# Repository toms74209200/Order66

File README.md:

<h1 style="text-align: center; margin-top: 0; margin-bottom: 7rem; border-bottom: none;">Order66 - 日本語入力のための60%キーボード</h1>

- 66 keys
- Cherry MX/Kailh Choc/Kailh Choc V2 key switch compatible
- USB type-C (USB2.0) interface
- On-Board CPU(ATmega32U4)

## Layout

Designed in [Keyboard-layout-editor.com](http://www.keyboard-layout-editor.com).

## License

MIT License

## Author

[toms74209200](<https://github.com/toms74209200>)

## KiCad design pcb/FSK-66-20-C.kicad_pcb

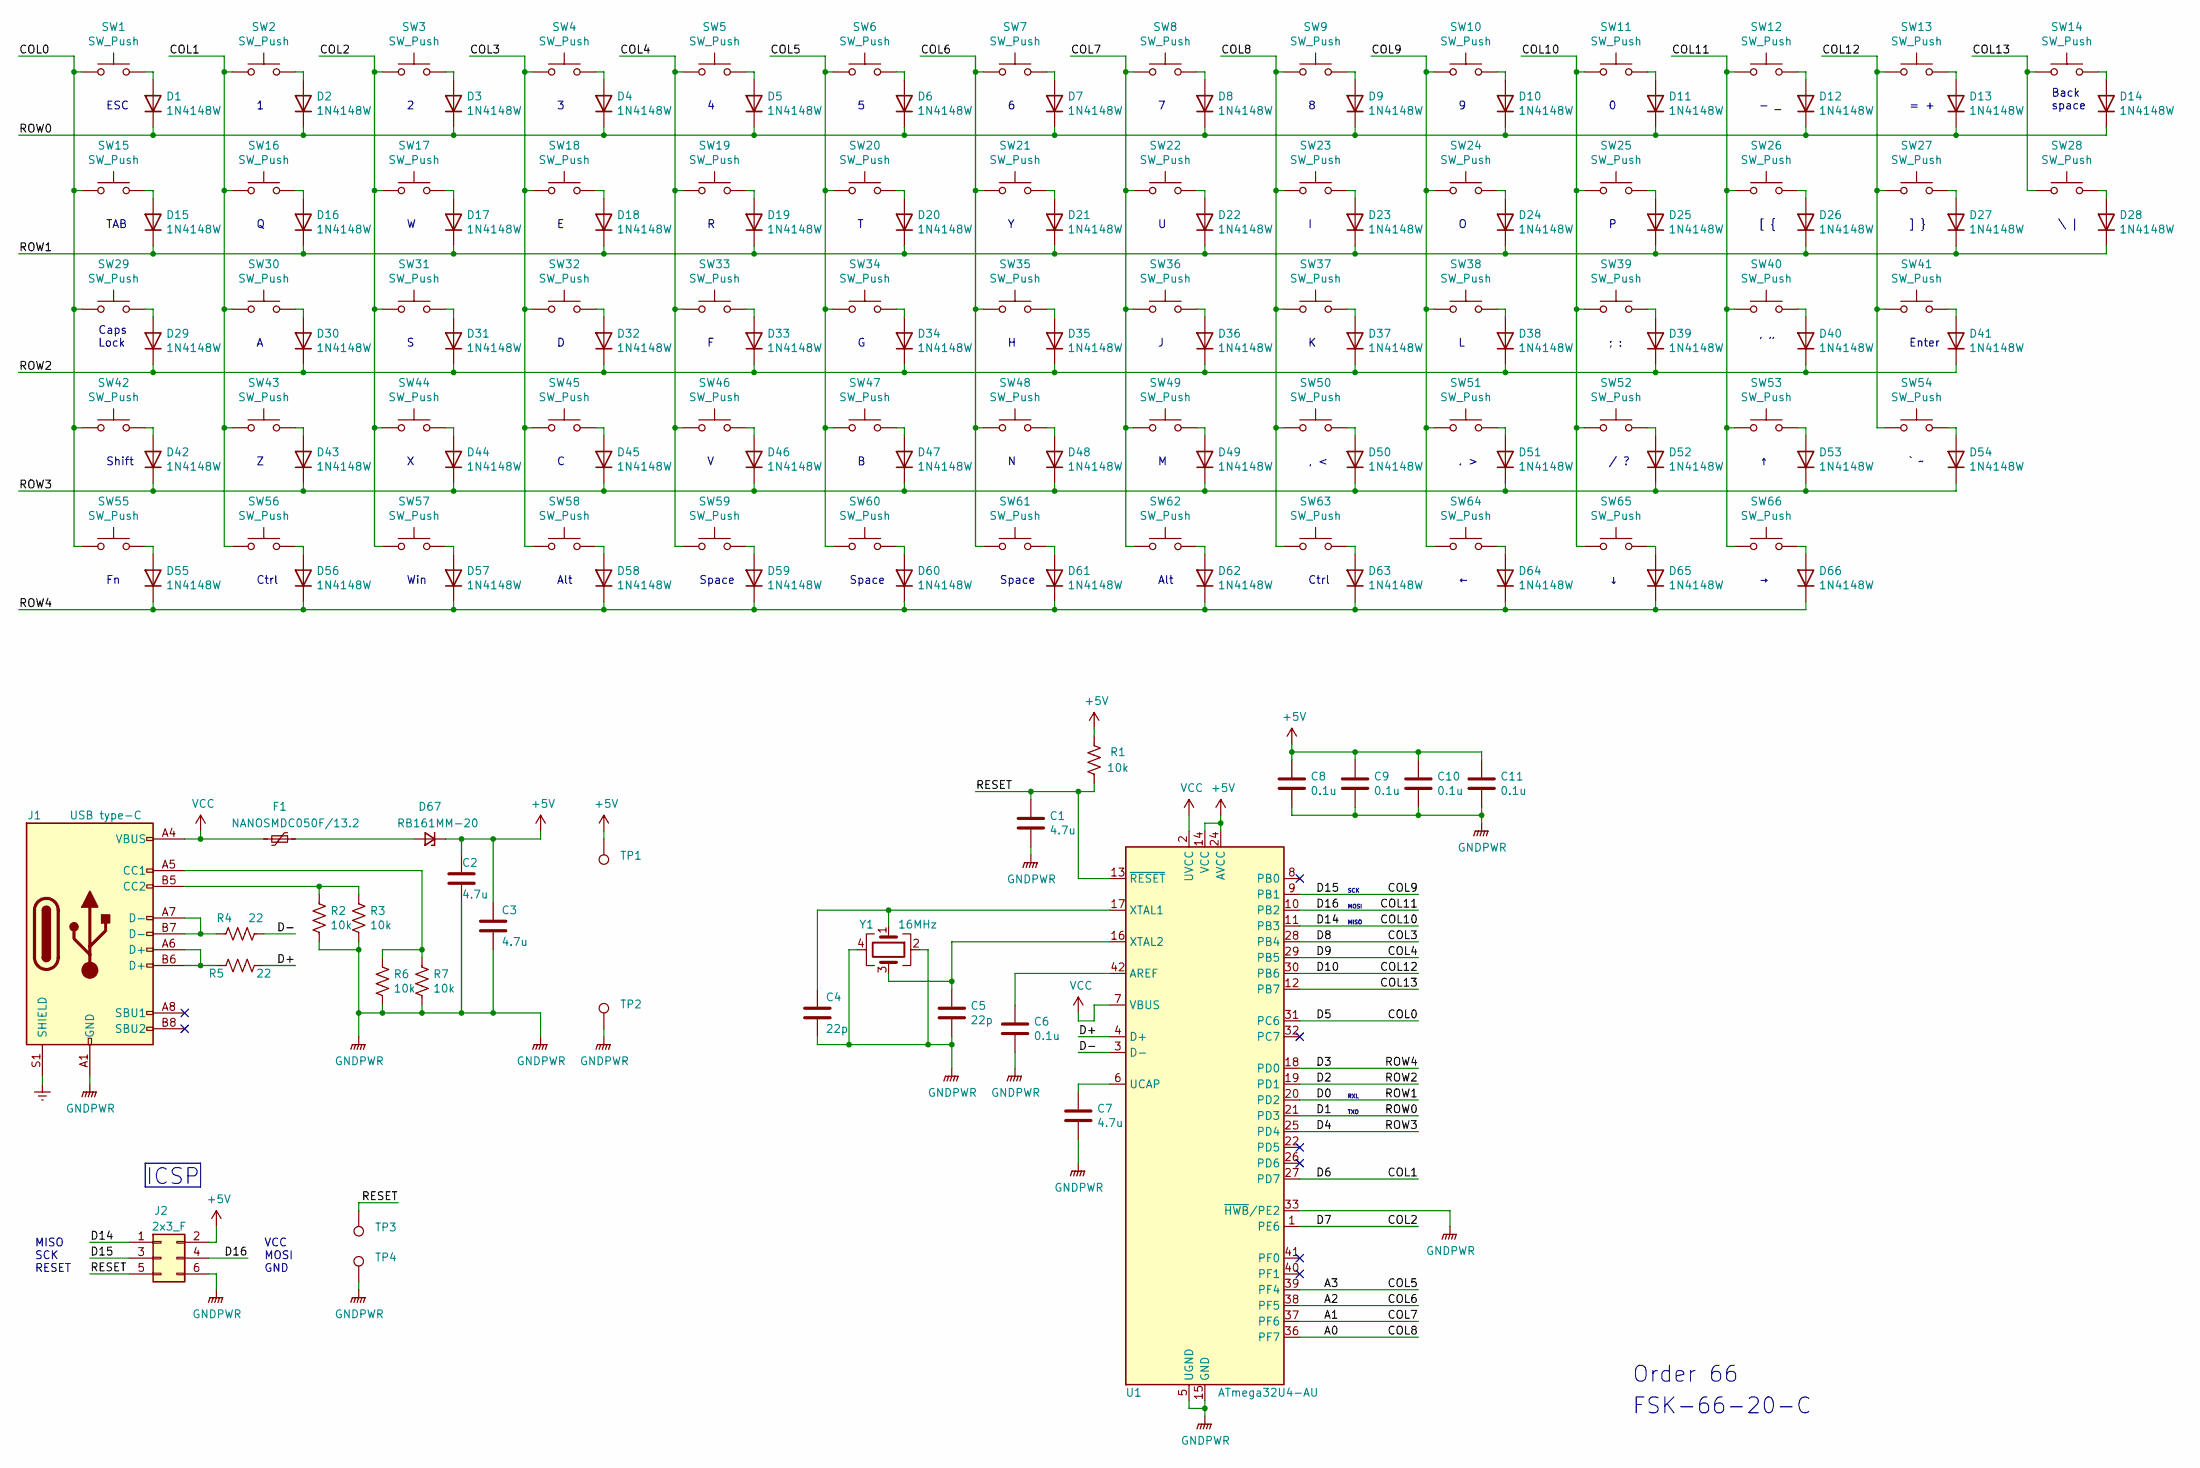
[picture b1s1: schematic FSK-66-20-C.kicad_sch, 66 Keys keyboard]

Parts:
C1, C2, C3, C7: 4.7u; C_0603_1608Metric
C4, C5: 22p; C_0402_1005Metric
C6, C8, C9, C10, C11: 0.1u; C_0402_1005Metric
D1, D2, D3, D4, D5, D6, D7, D8, D9, D10, D11, D12, D13, D14, D15, D16, D17, D18, D19, D20, D21, D22, D23, D24, D25, D26, D27, D28, D29, D30, D31, D32, D33, D34, D35, D36, D37, D38, D39, D40, D41, D42, D43, D44, D45, D46, D47, D48, D49, D50, D51, D52, D53, D54, D55, D56, D57, D58, D59, D60, D61, D62, D63, D64, D65, D66: 1N4148W; D_SOD-123
D67: RB161MM-20; D_SOD-123F
F1: NANOSMDC050F/13.2; Fuse_1206_3216Metric
J1: USB type-C; USB_C_Receptacle_Palconn_UTC16-G
J2: 2x3_F; PinHeader_2x03_P2.54mm_Vertical
R1, R2, R3, R6, R7: 10k; R_0402_1005Metric
R4, R5: 22; R_0402_1005Metric
SW1, SW2, SW3, SW4, SW5, SW6, SW7, SW8, SW9, SW10, SW11, SW12, SW13, SW14, SW15, SW16, SW17, SW18, SW19, SW20, SW21, SW22, SW23, SW24, SW25, SW26, SW27, SW28, SW29, SW30, SW31, SW32, SW33, SW34, SW35, SW36, SW37, SW38, SW39, SW40, SW41, SW42, SW43, SW44, SW45, SW46, SW47, SW48, SW49, SW50, SW51, SW52, SW53, SW54, SW55, SW56, SW57, SW58, SW59, SW60, SW61, SW62, SW63, SW64, SW65, SW66: SW_Push; CherryMX_Choc_V2_1u
TP1, TP2, TP3, TP4: TestPoint_THTPad_D1.0mm_Drill0.5mm
U1: ATmega32U4-AU; ATMEGA32U4-AU
Y1: 16MHz; Crystal_SMD_SeikoEpson_FA238-4Pin_3.2x2.5mm

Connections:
+5V: C2.1, C3.1, C8.1, C9.1, C10.1, C11.1, D67.1 (K), J2.2, R1.1, TP1.1, U1.14 (VCC), U1.24 (AVCC), U1.34 (VCC), U1.44 (AVCC)
/A0: SW9.1, SW23.1, SW37.1, SW50.1, SW63.1, U1.36 (PF7)
/A1: SW8.1, SW22.1, SW36.1, SW49.1, SW62.1, U1.37 (PF6)
/A2: SW7.1, SW21.1, SW35.1, SW48.1, SW61.1, U1.38 (PF5)
/A3: SW6.1, SW20.1, SW34.1, SW47.1, SW60.1, U1.39 (PF4)
/COL0: SW1.1, SW15.1, SW29.1, SW42.1, SW55.1, U1.31 (PC6)
/COL1: SW2.1, SW16.1, SW30.1, SW43.1, SW56.1, U1.27 (PD7)
/COL2: SW3.1, SW17.1, SW31.1, SW44.1, SW57.1, U1.1 (PE6)
/COL3: SW4.1, SW18.1, SW32.1, SW45.1, SW58.1, U1.28 (PB4)
/COL4: SW5.1, SW19.1, SW33.1, SW46.1, SW59.1, U1.29 (PB5)
/COL9: J2.3, SW10.1, SW24.1, SW38.1, SW51.1, SW64.1, U1.9 (PB1)
/COL10: J2.1, SW11.1, SW25.1, SW39.1, SW52.1, SW65.1, U1.11 (PB3)
/COL11: J2.4, SW12.1, SW26.1, SW40.1, SW53.1, SW66.1, U1.10 (PB2)
/COL12: SW13.1, SW27.1, SW41.1, SW54.1, U1.30 (PB6)
/COL13: SW14.1, SW28.1, U1.12 (PB7)
/D0: D15.1 (K), D16.1 (K), D17.1 (K), D18.1 (K), D19.1 (K), D20.1 (K), D21.1 (K), D22.1 (K), D23.1 (K), D24.1 (K), D25.1 (K), D26.1 (K), D27.1 (K), D28.1 (K), U1.20 (PD2)
/D1: D1.1 (K), D2.1 (K), D3.1 (K), D4.1 (K), D5.1 (K), D6.1 (K), D7.1 (K), D8.1 (K), D9.1 (K), D10.1 (K), D11.1 (K), D12.1 (K), D13.1 (K), D14.1 (K), U1.21 (PD3)
/D2: D29.1 (K), D30.1 (K), D31.1 (K), D32.1 (K), D33.1 (K), D34.1 (K), D35.1 (K), D36.1 (K), D37.1 (K), D38.1 (K), D39.1 (K), D40.1 (K), D41.1 (K), U1.19 (PD1)
/D3: D55.1 (K), D56.1 (K), D57.1 (K), D58.1 (K), D59.1 (K), D60.1 (K), D61.1 (K), D62.1 (K), D63.1 (K), D64.1 (K), D65.1 (K), D66.1 (K), U1.18 (PD0)
/D4: D42.1 (K), D43.1 (K), D44.1 (K), D45.1 (K), D46.1 (K), D47.1 (K), D48.1 (K), D49.1 (K), D50.1 (K), D51.1 (K), D52.1 (K), D53.1 (K), D54.1 (K), U1.25 (PD4)
/D+: R5.1, U1.4 (D+)
/D-: R4.1, U1.3 (D-)
/RESET: C1.1, J2.5, R1.2, TP3.1, U1.13 (~RESET)
Earth: J1.S1 (SHIELD)
GNDPWR: C1.2, C2.2, C3.2, C4.2, C5.2, C6.2, C7.2, C8.2, C9.2, C10.2, C11.2, J1.A1 (GND), J1.A12 (GND), J1.B1 (GND), J1.B12 (GND), J2.6, R2.2, R3.2, R6.2, R7.2, TP2.1, TP4.1, U1.5 (UGND), U1.15 (GND), U1.23 (GND), U1.33 (~HWB/PE2), U1.35 (GND), U1.43 (GND), Y1.2, Y1.4
unnamed: D1.2 (A), SW1.2
unnamed: D2.2 (A), SW2.2
unnamed: D3.2 (A), SW3.2
unnamed: D4.2 (A), SW4.2
unnamed: D5.2 (A), SW5.2
unnamed: D6.2 (A), SW6.2
unnamed: D7.2 (A), SW7.2
unnamed: D8.2 (A), SW8.2
unnamed: D9.2 (A), SW9.2
unnamed: D10.2 (A), SW10.2
unnamed: D11.2 (A), SW11.2
unnamed: D12.2 (A), SW12.2
unnamed: D13.2 (A), SW13.2
unnamed: D14.2 (A), SW14.2
unnamed: D15.2 (A), SW15.2
unnamed: D16.2 (A), SW16.2
unnamed: D17.2 (A), SW17.2
unnamed: D18.2 (A), SW18.2
unnamed: D19.2 (A), SW19.2
unnamed: D20.2 (A), SW20.2
unnamed: D21.2 (A), SW21.2
unnamed: D22.2 (A), SW22.2
unnamed: D23.2 (A), SW23.2
unnamed: D24.2 (A), SW24.2
unnamed: D25.2 (A), SW25.2
unnamed: D26.2 (A), SW26.2
unnamed: D27.2 (A), SW27.2
unnamed: D28.2 (A), SW28.2
unnamed: D29.2 (A), SW29.2
unnamed: D30.2 (A), SW30.2
unnamed: D31.2 (A), SW31.2
unnamed: D32.2 (A), SW32.2
unnamed: D33.2 (A), SW33.2
unnamed: D34.2 (A), SW34.2
unnamed: D35.2 (A), SW35.2
unnamed: D36.2 (A), SW36.2
unnamed: D37.2 (A), SW37.2
unnamed: D38.2 (A), SW38.2
unnamed: D39.2 (A), SW39.2
unnamed: D40.2 (A), SW40.2
unnamed: D41.2 (A), SW41.2
unnamed: D42.2 (A), SW42.2
unnamed: D43.2 (A), SW43.2
unnamed: D44.2 (A), SW44.2
unnamed: D45.2 (A), SW45.2
unnamed: D46.2 (A), SW46.2
unnamed: D47.2 (A), SW47.2
unnamed: D48.2 (A), SW48.2
unnamed: D49.2 (A), SW49.2
unnamed: D50.2 (A), SW50.2
unnamed: D51.2 (A), SW51.2
unnamed: D52.2 (A), SW52.2
unnamed: D53.2 (A), SW53.2
unnamed: D54.2 (A), SW54.2
unnamed: D55.2 (A), SW55.2
unnamed: D56.2 (A), SW56.2
unnamed: D57.2 (A), SW57.2
unnamed: D58.2 (A), SW58.2
unnamed: D59.2 (A), SW59.2
unnamed: D60.2 (A), SW60.2
unnamed: D61.2 (A), SW61.2
unnamed: D62.2 (A), SW62.2
unnamed: D63.2 (A), SW63.2
unnamed: D64.2 (A), SW64.2
unnamed: D65.2 (A), SW65.2
unnamed: D66.2 (A), SW66.2
unnamed: D67.2 (A), F1.1
unnamed: J1.A5 (CC1), R6.1, R7.1
unnamed: J1.B5 (CC2), R2.1, R3.1
unnamed: J1.A6 (D+), J1.B6 (D+), R5.2
unnamed: J1.A7 (D-), J1.B7 (D-), R4.2
unnamed: C6.1, U1.42 (AREF)
unnamed: C7.1, U1.6 (UCAP)
unnamed: C4.1, U1.17 (XTAL1), Y1.1
unnamed: C5.1, U1.16 (XTAL2), Y1.3
VCC: F1.2, J1.A4 (VBUS), J1.A9 (VBUS), J1.B4 (VBUS), J1.B9 (VBUS), U1.2 (UVCC), U1.7 (VBUS)

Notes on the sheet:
] }
Win
- _
Caps Lock
Alt
/ ?
TAB
MOSI
Ctrl
= +
Space
‘ “
TXO
\ |
ICSP
Enter
Order 66
SCK
MISO SCK RESET
Shift
; :
. >
ESC
RXL
` ~
, <
MISO
[ {
Back space
VCC MOSI GND
FSK-66-20-C

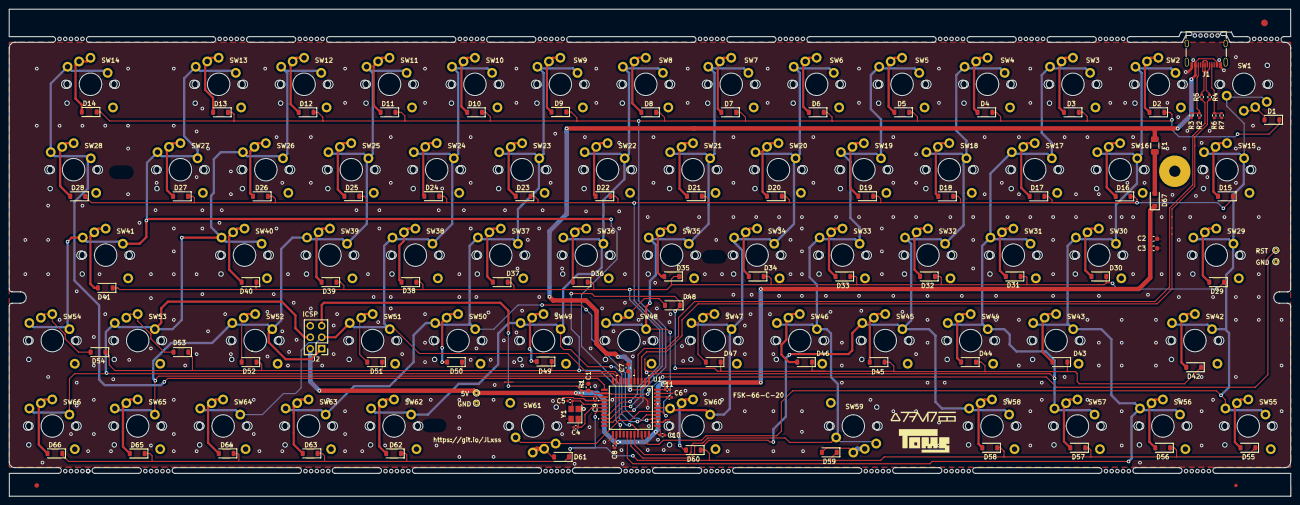
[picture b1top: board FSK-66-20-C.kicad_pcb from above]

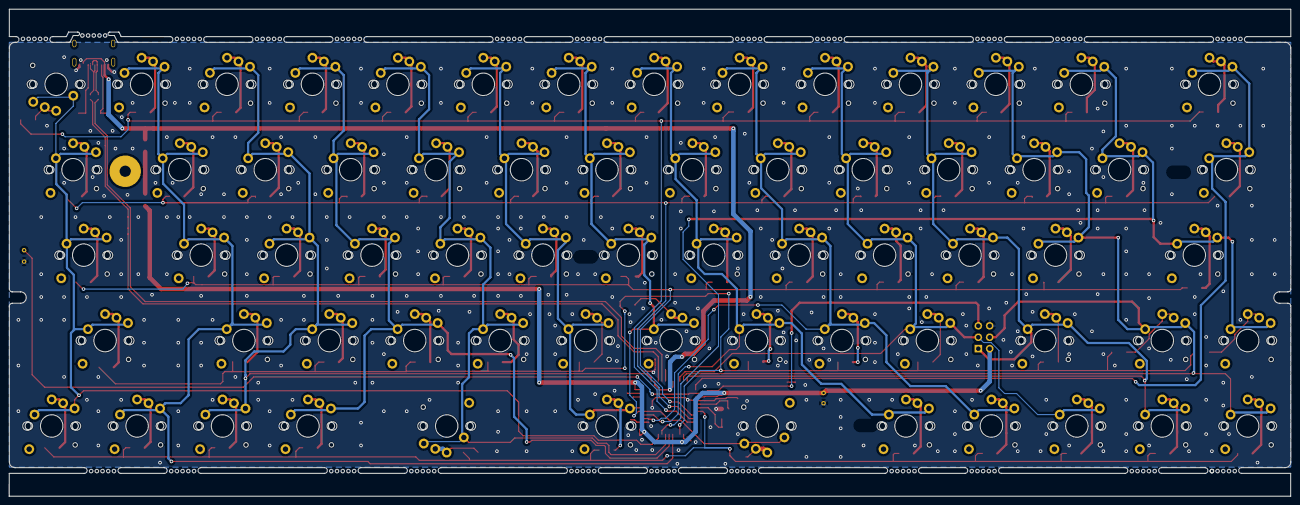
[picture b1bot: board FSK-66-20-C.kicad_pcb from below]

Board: 2 copper layers, 285.0 x 108.3 mm, 164 parts (66 on the bottom side), 100 nets.

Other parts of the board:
HOLE: VAL**; PKRH
HOLE#2, HOLE#3: VAL**; PKRH
HOLE#4: VAL**; PKRHC

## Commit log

2020-12-29 [add]add schematic
2020-12-29 [add]add keyboard layout file
2020-12-29 [docs]add README
2020-12-29 [add]add gitignore
2020-12-30 [fix]fix connection of CC2
2020-12-31 [fix]fix cross connection
2021-01-02 [fix]fix COL1 connection
2021-01-07 [add]add PCB
2021-01-07 [add]add ignore file
2021-01-11 [change]change side holes to no-plated
2021-08-09 [change]change layout
2021-08-09 [add]add firmware
2021-08-09 [add]add HEX file
2023-12-29 [change]change artwork
2024-01-20 [change]update artwork for board drill
2024-02-10 [change]updage keymap
2024-05-19 :sparkles: Update schematic
2024-05-19 :fire: Remove old version files
2024-05-23 :see_no_evil: Add gitignore
2024-05-26 :sparkles: Update PCB
2024-06-05 :sparkles: Add switch plate
2024-06-17 :sparkles: Update firmware
2024-08-22 :hammer: Add development settings
2024-08-22 :sparkles: Add Astro project
2024-08-23 :heavy_plus_sign: Update dependencies
2024-08-23 :hammer: Update devcontainer settings
2024-08-23 :sparkles: Add index page
2024-08-24 :sparkles: Add favicon
2024-08-25 :construction_worker: Add workflow for deploy GitHub pages
2024-08-25 :construction_worker: Fix deploy pages workflow to adding permissions
2024-08-26 :bug: Fix resolve resources
2024-08-29 :memo: Update README
2024-08-29 :construction_worker: Update deploy workflow trigger
2024-08-31 :sparkles: Update docs
2024-08-31 :bug: Fix OGP image
2024-09-19 :sparkles: Update PCB for Kailh Choc stabilizer
2024-09-20 :sparkles: Update switch plate for Kailh Choc stabilizer
2024-10-06 :sparkles: Add middle plate
2024-10-06 :sparkles: Update top key switch plate
2024-10-06 :see_no_evil: Update gitignore
2025-03-25 :sparkles: Update middle plate
2025-03-25 :sparkles: Update top plate
